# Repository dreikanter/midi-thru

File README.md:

# MIDI Thru

A little MIDI splitter that you can build on a breadboard in an hour or so.

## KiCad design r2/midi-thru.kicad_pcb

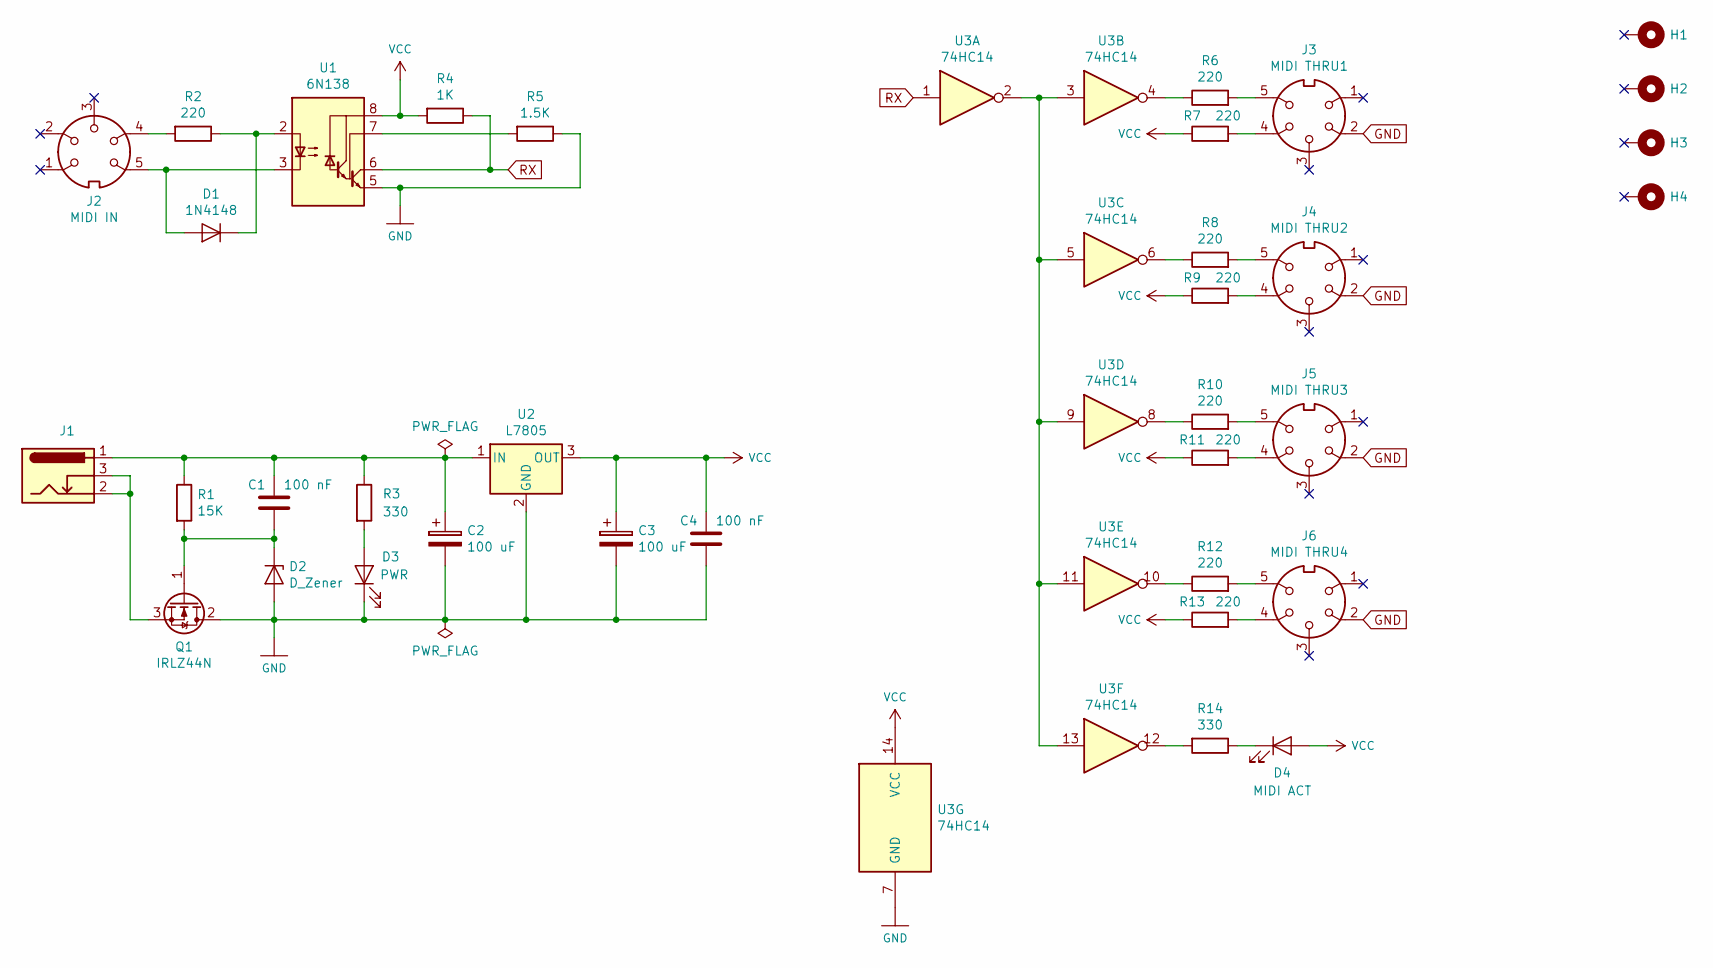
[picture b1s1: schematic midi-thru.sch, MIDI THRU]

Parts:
C1, C4: 100 nF; C_Disc_D5.0mm_W2.5mm_P5.00mm
C2, C3: 100 uF; CP_Radial_D6.3mm_P2.50mm
D1: 1N4148; D_DO-35_SOD27_P7.62mm_Horizontal
D2: D_Zener; D_DO-35_SOD27_P7.62mm_Horizontal
D3: PWR; LED_D5.0mm
D4: MIDI ACT; LED_D5.0mm
H1, H2, H3, H4: MountingHole_Pad; MountingHole_3mm_Pad_Via
J1: Barrel_Jack_Switch; BarrelJack_Horizontal
J2: MIDI IN; din-5
J3: MIDI THRU1; din-5
J4: MIDI THRU2; din-5
J5: MIDI THRU3; din-5
J6: MIDI THRU4; din-5
Q1: IRLZ44N; TO-220-3_Vertical
R1: 15K; R_Axial_DIN0204_L3.6mm_D1.6mm_P7.62mm_Horizontal
R2, R6, R7, R8, R9, R10, R11, R12, R13: 220; R_Axial_DIN0204_L3.6mm_D1.6mm_P7.62mm_Horizontal
R3, R14: 330; R_Axial_DIN0204_L3.6mm_D1.6mm_P7.62mm_Horizontal
R4: 1K; R_Axial_DIN0204_L3.6mm_D1.6mm_P7.62mm_Horizontal
R5: 1.5K; R_Axial_DIN0204_L3.6mm_D1.6mm_P7.62mm_Horizontal
U1: 6N138; DIP-8_W7.62mm_Socket
U2: L7805; TO-220-3_Vertical
U3: 74HC14; DIP-14_W7.62mm_Socket

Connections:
GND: C2.2, C3.2, C4.2, D2.2 (A), D3.1 (K), J3.2, J4.2, J5.2, J6.2, Q1.2 (D), R5.1, U1.5 (GND), U2.2 (GND), U3.7 (GND)
unnamed: C1.1, C2.1, J1.1, R1.1, R3.1, U2.1 (IN)
unnamed: C1.2, D2.1 (K), Q1.1 (G), R1.2
unnamed: D1.1 (K), R2.1, U1.2 (C1)
unnamed: D1.2 (A), J2.5, U1.3 (C2)
unnamed: D3.2 (A), R3.2
unnamed: D4.1 (K), R14.1
unnamed: J1.2, J1.3, Q1.3 (S)
unnamed: J2.4, R2.2
unnamed: J3.4, R7.2
unnamed: J3.5, R6.2
unnamed: J4.4, R9.2
unnamed: J4.5, R8.2
unnamed: J5.4, R11.2
unnamed: J5.5, R10.2
unnamed: J6.4, R13.2
unnamed: J6.5, R12.2
unnamed: R5.2, U1.7 (VO1)
unnamed: R6.1, U3.4
unnamed: R8.1, U3.6
unnamed: R10.1, U3.8
unnamed: R12.1, U3.10
unnamed: R14.2, U3.12
unnamed: U3.2, U3.3, U3.5, U3.9, U3.11, U3.13
RX: R4.1, U1.6 (VO2), U3.1
VCC: C3.1, C4.1, D4.2 (A), R4.2, R7.1, R9.1, R11.1, R13.1, U1.8 (VCC), U2.3 (OUT), U3.14 (VCC)

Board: 2 copper layers, 37 parts (0 on the bottom side), 26 nets, no tracks yet.

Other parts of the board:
LOGO_OSHW_silkscreen_5mm: val**; LOGO_OSHW_silkscreen_5mm

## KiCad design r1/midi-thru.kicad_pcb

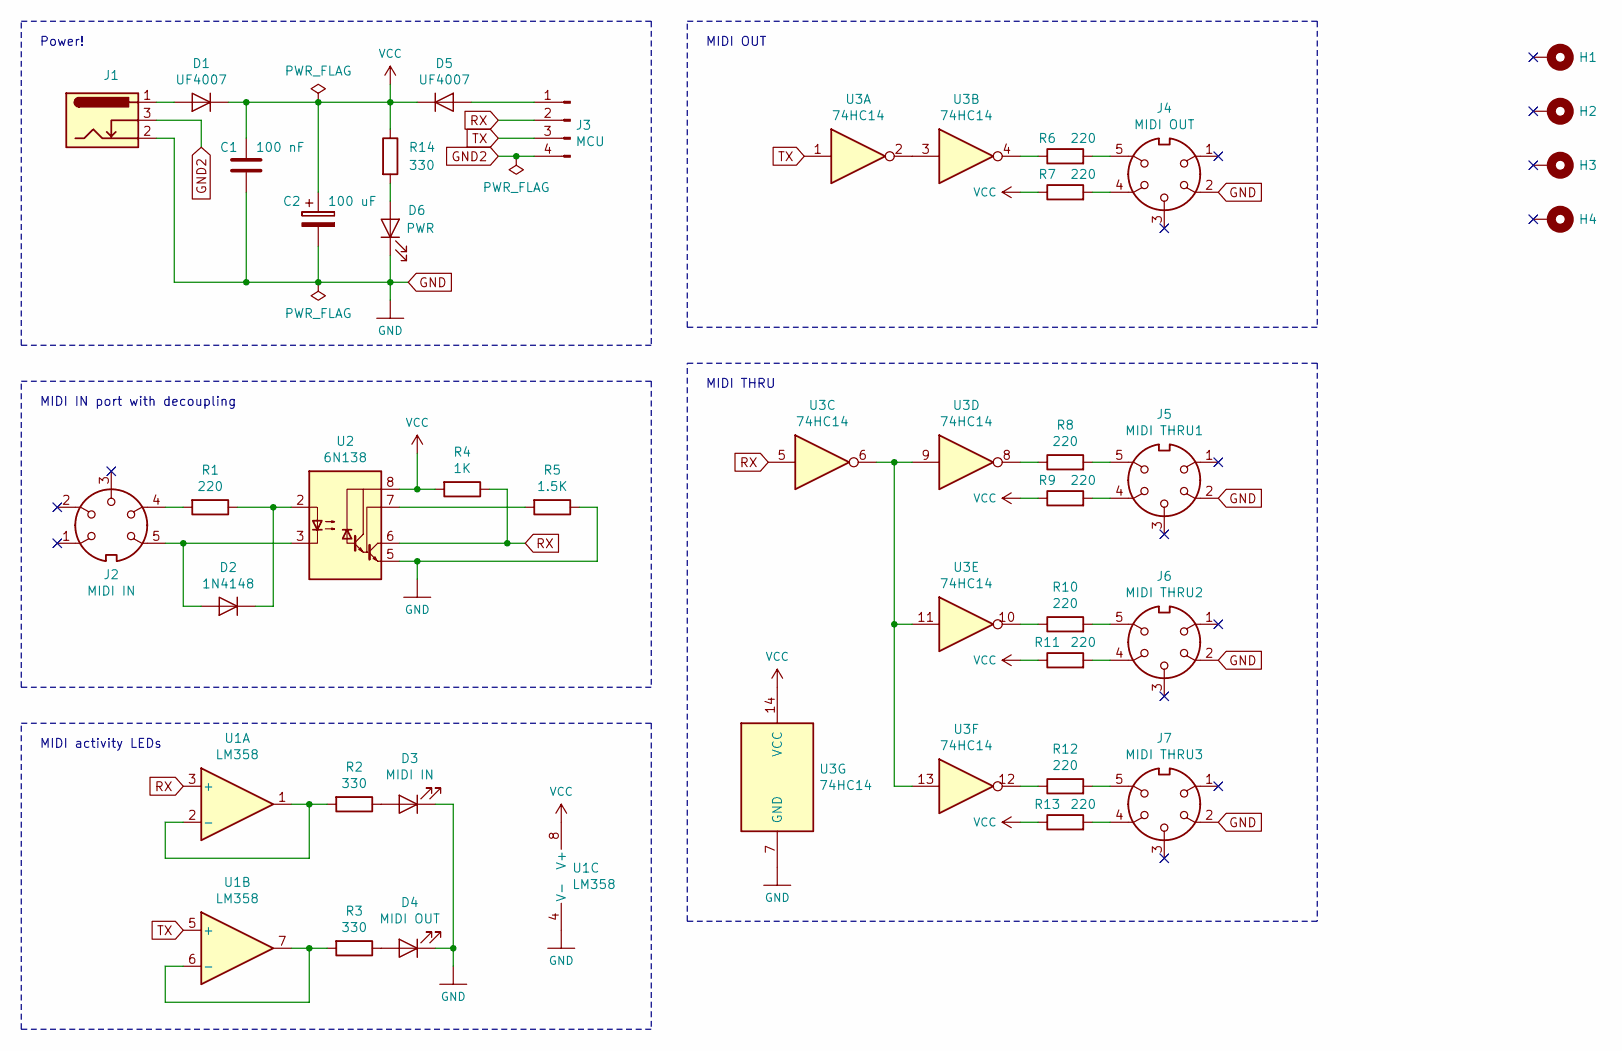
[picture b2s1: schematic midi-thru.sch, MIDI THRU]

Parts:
C1: 100 nF; C_Disc_D5.0mm_W2.5mm_P5.00mm
C2: 100 uF; CP_Radial_D5.0mm_P2.50mm
D1, D5: UF4007; D_DO-41_SOD81_P10.16mm_Horizontal
D2: 1N4148; D_DO-35_SOD27_P7.62mm_Horizontal
D3: MIDI IN; LED_D5.0mm
D4: MIDI OUT; LED_D5.0mm
D6: PWR; LED_D5.0mm
H1, H2, H3, H4: MountingHole_Pad; MountingHole_3mm_Pad_Via
J1: Barrel_Jack_Switch; BarrelJack_Horizontal
J2: MIDI IN; din-5
J3: MCU; 1X04
J4: MIDI OUT; din-5
J5: MIDI THRU1; din-5
J6: MIDI THRU2; din-5
J7: MIDI THRU3; din-5
R1, R6, R7, R8, R9, R10, R11, R12, R13: 220; R_Axial_DIN0204_L3.6mm_D1.6mm_P7.62mm_Horizontal
R2, R3, R14: 330; R_Axial_DIN0204_L3.6mm_D1.6mm_P7.62mm_Horizontal
R4: 1K; R_Axial_DIN0204_L3.6mm_D1.6mm_P7.62mm_Horizontal
R5: 1.5K; R_Axial_DIN0204_L3.6mm_D1.6mm_P7.62mm_Horizontal
U1: LM358; DIP-8_W7.62mm_Socket
U2: 6N138; DIP-8_W7.62mm_Socket
U3: 74HC14; DIP-14_W7.62mm_Socket

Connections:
GND: C1.2, C2.2, D3.1 (K), D4.1 (K), D6.1 (K), J1.2, J4.2, J5.2, J6.2, J7.2, R5.1, U1.4 (V-), U2.5 (GND), U3.7 (GND)
GND2: J1.3, J3.4
unnamed: D1.2 (A), J1.1
unnamed: D2.1 (K), R1.1, U2.2 (C1)
unnamed: D2.2 (A), J2.5, U2.3 (C2)
unnamed: D3.2 (A), R2.1
unnamed: D4.2 (A), R3.1
unnamed: D5.2 (A), J3.1
unnamed: D6.2 (A), R14.2
unnamed: J2.4, R1.2
unnamed: J4.4, R7.2
unnamed: J4.5, R6.2
unnamed: J5.4, R9.2
unnamed: J5.5, R8.2
unnamed: J6.4, R11.2
unnamed: J6.5, R10.2
unnamed: J7.4, R13.2
unnamed: J7.5, R12.2
unnamed: R2.2, U1.1, U1.2 (-)
unnamed: R3.2, U1.6 (-), U1.7
unnamed: R5.2, U2.7 (VO1)
unnamed: R6.1, U3.4
unnamed: R8.1, U3.8
unnamed: R10.1, U3.10
unnamed: R12.1, U3.12
unnamed: U3.2, U3.3
unnamed: U3.6, U3.9, U3.11, U3.13
RX: J3.2, R4.1, U1.3 (+), U2.6 (VO2), U3.5
TX: J3.3, U1.5 (+), U3.1
VCC: C1.1, C2.1, D1.1 (K), D5.1 (K), R4.2, R7.1, R9.1, R11.1, R13.1, R14.1, U1.8 (V+), U2.8 (VCC), U3.14 (VCC)

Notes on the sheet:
MIDI IN port with decoupling
MIDI activity LEDs
MIDI OUT
MIDI THRU
Power!

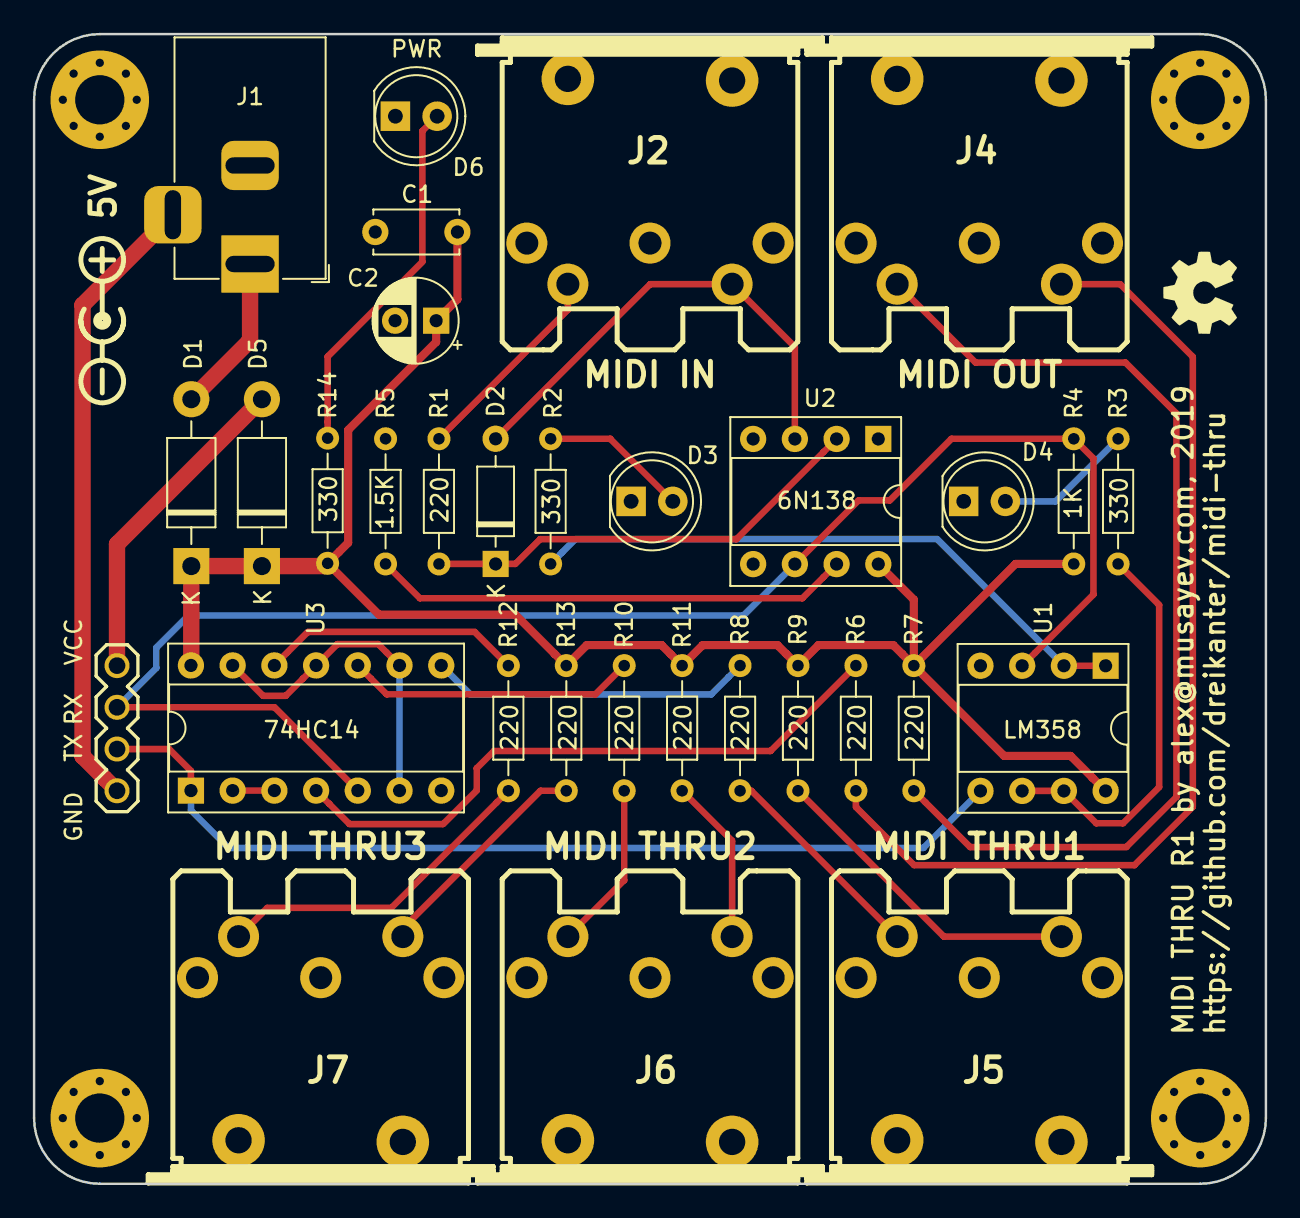
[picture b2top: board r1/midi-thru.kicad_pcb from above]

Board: 2 copper layers, 75.0 x 70.0 mm, 37 parts (0 on the bottom side), 30 nets.

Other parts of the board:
LOGO_OSHW_silkscreen_5mm: val**; LOGO_OSHW_silkscreen_5mm

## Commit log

2019-04-22 R1 schematic and PCB design
2019-04-29 Revision 2
2019-04-29 Update schematics PDF
2019-04-29 Add voltage regulator
2019-05-01 Update PDF schematics
